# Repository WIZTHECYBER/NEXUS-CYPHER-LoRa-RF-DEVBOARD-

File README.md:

# 🛰️ NEXUS CYPHER: RP2040 LoRa RF Devboard

Yo! Welcome to the **Nexus Cypher**. 

I designed this board, and ngl, getting it to the finish line was a massive reality check. This repo doesn't just have the final manufacturing files—it’s the actual log of every time I got humbled by the reviewers and the factory robots. If you're designing your first complex RF board, please learn from my mistakes so you don't get kicked back as much as I did.

## 💡 What I Actually Made
The Nexus Cypher is a custom, open-source Long Range (LoRa) radio frequency devboard. I wanted a flexible, overpowered platform for RF hacking and experiments. 

**The Specs:**
* **Brain:** Raspberry Pi RP2040
* **Radio:** Semtech SX1262 (LoRa)
* **RF Switch:** PE4259 (UltraCMOS SPDT)
* **Storage:** W25Q128JVS (128M-bit Flash)
* **Power:** AP2112K-3.3V LDO
* **Extras:** USB-C, 0.96" OLED header, Reset & Boot buttons.

## Schematics 

## PCB routing 

## FINAL PCB 

## 💀 The "Wall of Shame" (Dev Journal)
I spent like 16 hours hyper-focusing on impedance matching and RF traces. I thought I was a genius. Then I submitted it for review and got hit with reality. Here is everything that went wrong and how I fixed it:

### 1. Forgetting humans actually hold these boards
I was so zoomed in on the physics of the RF traces that I completely ignored the physical board itself. 
* **The Roast:** The reviewer literally told me to *"Please neaten up your board a bit with silkscreen, rounded corners, ect."*. 
* **The Fix:** I had sharp 90-degree corners that would probably slice my hand open, and I just slapped my text (`R1`, `C12`, etc.) right on top of my carefully routed traces. I had to go back into KiCad, draw smooth arcs on the `Edge.Cuts` layer, and individually move every single piece of text so the factory could actually print it.

### 2. Asking for way too much money
I was submitting this for a hardware grant and totally fumbled the math.
* **The Roast:** *"Your bom cost is unrealistic you cant be requesting this number... please resubmit with the correcct tier"*.
* **The Fix:** Bruh, you can't just guess your numbers. I had to actually calculate the real-world cost of the RP2040, the LoRa IC, and the JLCPCB assembly fees, and request the correct tier that matched reality.

### 3. Excel cooked my BOM
I thought exporting a Bill of Materials (BOM) was just a one-click thing. 
* **The Roast:** The reviewer just straight up said *"your BOM.csv is broken"*.
* **The Fix:** Excel completely mangled my CSV file. All my capacitors (`C1`, `C8`, `C9`) spilled across 10 different columns, and it used semicolons instead of commas. Also, I learned that JLCPCB factory robots don't read English—they just match text. I had to manually sanitize the entire spreadsheet so the Pick & Place machines wouldn't throw an error. 

### 4. The "Ghost" Repo
I assumed the hardware spoke for itself and left everything blank.
* **The Roast:** *"your ReadME is missing description about your project. Your journals are also not descriptive enough, you need to explain what you did what went well / wrong etc"*.
* **The Fix:** Open-source hardware is literally useless if nobody knows *why* you built it or how it works. That's exactly why I'm writing this massive README right now.

## 🗂️ Files in this Repo
* `/Nexus Cypher production/` - The actual KiCad 9.0 source files.
* `Nexus cypher gerber.zip` - Production-ready Gerbers.
* `Nexus Cypher BOM.csv` - The sanitized, robot-approved Bill of Materials.
* `Nexus Cypher-all-pos.csv` - Pick & Place (CPL) file.

## ⚖️ License
This is open-source hardware, fr. 

* **Hardware:** Released under the **CERN Open Hardware Licence Version 2 - Strongly Reciprocal (CERN-OHL-S)**. You can use it, mod it, and fab it, but if you change it, you gotta share it under the same terms.
* **Docs/Software:** Released under the **MIT License**.

---
*Built by WIZTHECYBER.*

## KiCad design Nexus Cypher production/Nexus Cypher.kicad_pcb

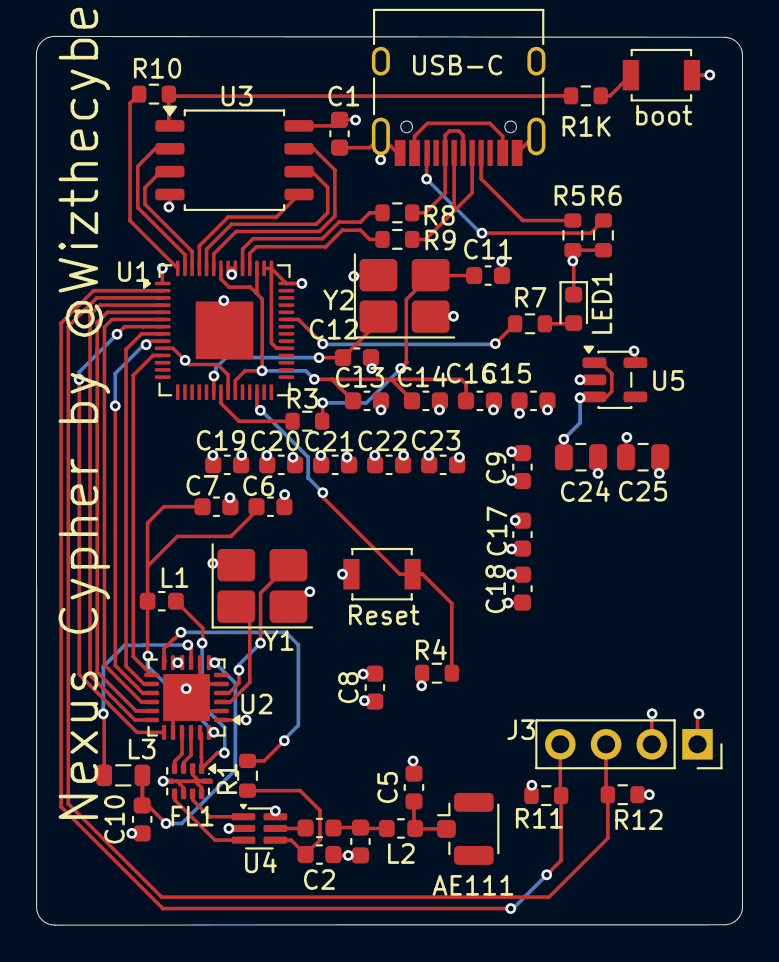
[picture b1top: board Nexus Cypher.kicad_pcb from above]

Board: 4 copper layers, 39.2 x 49.4 mm, 54 parts (0 on the bottom side), 49 nets.

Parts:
AE111: Antenna; U.FL_Hirose_U.FL-R-SMT-1_Vertical
C1, C8, C9, C13, C14, C17, C18, C19, C20, C21, C22: 100nF; C_0603_1608Metric
C2: 1nF; C_0603_1608Metric
C3: 39pF; C_0603_1608Metric
C4, C5: 3.3pF; C_0603_1608Metric
C6: 47pF; C_0603_1608Metric
C7: 47nF; C_0603_1608Metric
C10: 470nF; C_0603_1608Metric
C11, C12: 27pF; C_0603_1608Metric
C15, C16: 1uF; C_0603_1608Metric
C23: 100nf; C_0603_1608Metric
C24, C25: 10uF; C_0805_2012Metric
FL1: 0900FM15K0039; Balun_Johanson_0900FM15K0039
J3: Conn_01x04_Socket; PinSocket_1x04_P2.54mm_Vertical
L1: 47nH; L_0603_1608Metric
L2: 9.1nH; L_0603_1608Metric
L3: 15uH; L_0805_2012Metric
LED1: BLUE; LED_0603_1608Metric
R1: 100; R_0603_1608Metric
R1K, R3, R7: 1K; R_0603_1608Metric
R4, R10: 10K; R_0603_1608Metric
R5, R6: 5.1K; R_0603_1608Metric
R8, R9: 27 ohm; R_0603_1608Metric
R11, R12: 4.7K; R_0603_1608Metric
Reset: RESET; SW_SPST_B3U-1000P
U1: RP2040; QFN-56-1EP_7x7mm_P0.4mm_EP3.2x3.2mm
U2: SX1262IMLTRT; QFN-24-1EP_4x4mm_P0.5mm_EP2.6x2.6mm
U3: W25Q128JVS; SOIC-8_5.3x5.3mm_P1.27mm
U4: PE4259; SOT-363_SC-70-6
U5: AP2112K-3.3; SOT-23-5
USB-C: USB_C_Receptacle_USB2.0_16P; USB_C_Receptacle_HRO_TYPE-C-31-M-12
Y1: 32MHz; Crystal_SMD_3225-4Pin_3.2x2.5mm_HandSoldering
Y2: 12MHz; Crystal_SMD_3225-4Pin_3.2x2.5mm_HandSoldering
boot: BOOT; SW_SPST_B3U-1000P

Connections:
+1V1: C13.1, C14.1, C15.2, U1.23 (DVDD), U1.45 (VREG_VOUT), U1.50 (DVDD)
+3V3: C1.1, C8.2, C9.1, C16.1, C17.1, C18.1, C19.1, C20.1, C21.1, C22.1, C23.1, C25.1, J3.2, R4.1, R11.1, R12.1, U1.1 (IOVDD), U1.10 (IOVDD), U1.22 (IOVDD), U1.33 (IOVDD), U1.42 (IOVDD), U1.43 (ADC_AVDD), U1.44 (VREG_VIN), U1.48 (USB_VDD), U1.49 (IOVDD), U2.1 (VDD_IN), U2.10 (VBAT), U2.11 (VBAT_IO), U3.8 (VCC), U4.6 (VDD), U5.5 (VOUT)
/QSPI_SCLK: U1.52 (QSPI_SCLK), U3.6 (CLK)
/QSPI_SD0: U1.53 (QSPI_SD0), U3.5 (DI/IO_{0})
/QSPI_SD1: U1.55 (QSPI_SD1), U3.2 (DO/IO_{1})
/QSPI_SD2: U1.54 (QSPI_SD2), U3.3 (~WP/IO_{2})
/QSPI_SD3: U1.51 (QSPI_SD3), U3.7 (~HOLD/~RESET/IO_{3})
/QSPI_SS: R1K.2, R10.1, U3.1 (~CS)
/SPI_MISO: U1.6 (GPIO4), U2.16 (MISO)
/SPI_MOSI: U1.5 (GPIO3), U2.17 (MOSI)
/SPI_SCK: U1.4 (GPIO2), U2.18 (SCK)
/USB_D+: R8.2, U1.47 (USB_DP)
/USB_D-: R9.2, U1.46 (USB_DM)
/XX_BUSY: U1.8 (GPIO6), U2.14 (BUSY)
/XX_DIO1: U1.11 (GPIO8), U2.13 (DIO1)
/XX_DIO2: R1.1, U2.12 (DIO2)
/XX_IN: C12.2, U1.20 (XIN), Y2.1
/XX_NRST: U1.9 (GPIO7), U2.15 (~RESET)
/XX_NSS: U1.7 (GPIO5), U2.19 (NSS)
/XX_OUT: R3.2, U1.21 (XOUT)
/XX_RFI_N: FL1.3 (RFI_N), U2.22 (RFI_N)
/XX_RFI_P: FL1.4 (RFI_P), U2.21 (RFI_P)
/XX_RFO: FL1.1 (RFO), L1.2, U2.23 (RFO)
/XX_RUN: R4.2, Reset.2, U1.26 (RUN)
/XX_SCL: J3.3, R12.2, U1.3 (GPIO1)
/XX_SDA: J3.4, R11.2, U1.2 (GPIO0)
/XX_SW_RFI: FL1.6 (SW_RFI), U4.3 (RF2)
/XX_SW_RFO: FL1.8 (SW_RFO), U4.1 (RF1)
/XX_VR_PA: C6.1, C7.1, L1.1, U2.24 (VR_PA)
/XX_XTA: U2.3 (XTA), Y1.1
/XX_XTB: U2.4 (XTB), Y1.3
GND: C1.2, C2.2, C4.2, C5.2, C6.2, C7.2, C8.1, C9.2, C10.2, C11.2, C12.1, C13.2, C14.2, C15.1, C16.2, C17.2, C18.2, C19.2, C20.2, C21.2, C22.2, C23.2, C24.2, C25.2, FL1.2 (GND), FL1.5 (GND), FL1.7 (GND), FL1.9 (GND), FL1.10 (GND), J3.1, LED1.1 (K), R5.2, R6.2, Reset.1, U1.57 (GND), U2.2 (GND), U2.5 (GND), U2.8 (GND), U2.20 (GND), U2.25 (GND), U3.4 (GND), U4.2 (GND), U5.2 (GND), USB-C.A1 (GND), USB-C.A12 (GND), USB-C.B1 (GND), USB-C.B12 (GND), USB-C.S1 (SHIELD), Y1.2 (G), Y1.4 (G), Y2.2 (G), Y2.4 (G), boot.1
unnamed: AE111.1 (A_1), C5.1, L2.1
unnamed: C3.1, C4.1, L2.2
unnamed: C11.1, R3.1, Y2.3
unnamed: R5.1, USB-C.A5 (CC1)
unnamed: R6.1, USB-C.B5 (CC2)
unnamed: R8.1, USB-C.A6 (D+), USB-C.B6 (D+)
unnamed: R9.1, USB-C.A7 (D-), USB-C.B7 (D-)
unnamed: LED1.2 (A), R7.2
unnamed: R1K.1, boot.2
unnamed: R7.1, U1.37 (GPIO25)
unnamed: R10.2, U1.56 (~QSPI_SS)
unnamed: L3.1, U2.9 (DCC_SW)
unnamed: C10.1, L3.2, U2.7 (VREG)
unnamed: C2.1, R1.2, U4.4 (CTRL)
unnamed: C3.2, U4.5 (RFIN)
VBUS1: USB-C.A4 (VBUS), USB-C.A9 (VBUS), USB-C.B4 (VBUS), USB-C.B9 (VBUS)
VBUS2: C24.1, U5.1 (VIN), U5.3 (EN)

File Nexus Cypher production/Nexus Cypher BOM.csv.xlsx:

COMPONENTS | Footprints | Quantity | Designation AND VALUES | DESIGNATOR
1;AE111 | U.FL_Hirose_U.FL-R-SMT-1_Vertica | 1 | ANTENNA
2;"spst switch" | SW_SPST_B3U-1000P | 1 | boot button
3;"Capacitor 1, 8, 9, 13, 14, 17, 18, 19, 20, 21, 22" | C_0603_1608Metric | 11 | 100nF Capacitors
4;"Capacitor 2" | C_0603_1608Metric | 1 | 1nF Capacitor
5;"Capacitor 3" | C_0603_1608Metric | 1 | 39pF Ca[acitor
6;"Capacitor 4 , 5 | C_0603_1608Metric | 2 | 3.3pF Capacitor
7;"Capacitor 6" | C_0603_1608Metric | 1 | 47pF Capacitor
8;"Capacitor 7" | C_0603_1608Metric | 1 | 47nF Capacitor
9;"Capacitor 10" | C_0603_1608Metric | 1 | 470nF Capacitor
10;"Capacitor 11 , 12" | C_0603_1608Metric | 2 | 27pF Capacitor
11;"Capacitor 15, 16" | C_0603_1608Metric | 2 | 1uF Capacitor
12;"Capacitor 23" | C_0603_1608Metric | 1 | 100nF Capacitors
13;"Capacitor 24,25 | C_0805_2012Metric | 2 | 10uF Capacitor
14;"FL1" | Balun_Johanson_0900FM15K0039 | 1 | 0900FM15K0039
15;"0.96 oled display" | PinSocket_1x04_P2.54mm_Vertical | 1 | Conn_01x04_Socket
16;"L1 inductor 47nH" | L_0603_1608Metric | 1 | 47nH inductor
17;"L2 inductor 9.1nH" | L_0603_1608Metric | 1 | 9.1nH inductor
18;"L3 Inductor 15uH" | L_0805_2012Metric | 1 | 15uH inductor
19;"LED blue colour " | LED_0603_1608Metric | 1 | blue LED
20;"R1" | R_0603_1608Metric | 1 | 100 ohm
21;"R1K,R3 | R_0603_1608Metric | 3 | 1K ohm
22;"R4,10 | R_0603_1608Metric | 2 | 10K ohm
23;"R5 , 6 | R_0603_1608Metric | 2 | 5.1K ohm
24;"R8.9 | R_0603_1608Metric | 2 | 27 ohm
25;"R11,12 | R_0603_1608Metric | 2 | 4.7K ohm
26;"spdt switch " | SW_SPST_B3U-1000P | 1 | Reset button
27;"U1 RP2040" | QFN-56-1EP_7x7mm_P0.4mm_EP3.2x3.2mm | 1 | RP2040
28;"U2 SX1262IMLTRT" | QFN-24-1EP_4x4mm_P0.5mm_EP2.6x2.6mm | 1 | SX1262IMLTRT
29;"U3 W25Q128JVS" | SOIC-8_5.3x5.3mm_P1.27mm | 1 | W25Q128JVS
30;"U4 "PE4259" | SOT-363_SC-70-6 | 1 | PE4259
31;"U5 AP2112K-3.3" | SOT-23-5 | 1 | AP2112K-3.3
32;"USB-C_Receptacle_USB2.0_16P" | USB_C_Receptacle_HRO_TYPE-C-31-M-12 | 1 | USB-C_Receptacle_USB2.0_16P
33;"Y1 CRYSTAL 32MHz" | Crystal_SMD_3225-4Pin_3.2x2.5mm_HandSoldering | 1 | CRYSTAL 32MHz
34;"Y2 CRYSTAL 12mHZ" | Crystal_SMD_3225-4Pin_3.2x2.5mm_HandSoldering | 1 | CRYSTAL 12MHz
